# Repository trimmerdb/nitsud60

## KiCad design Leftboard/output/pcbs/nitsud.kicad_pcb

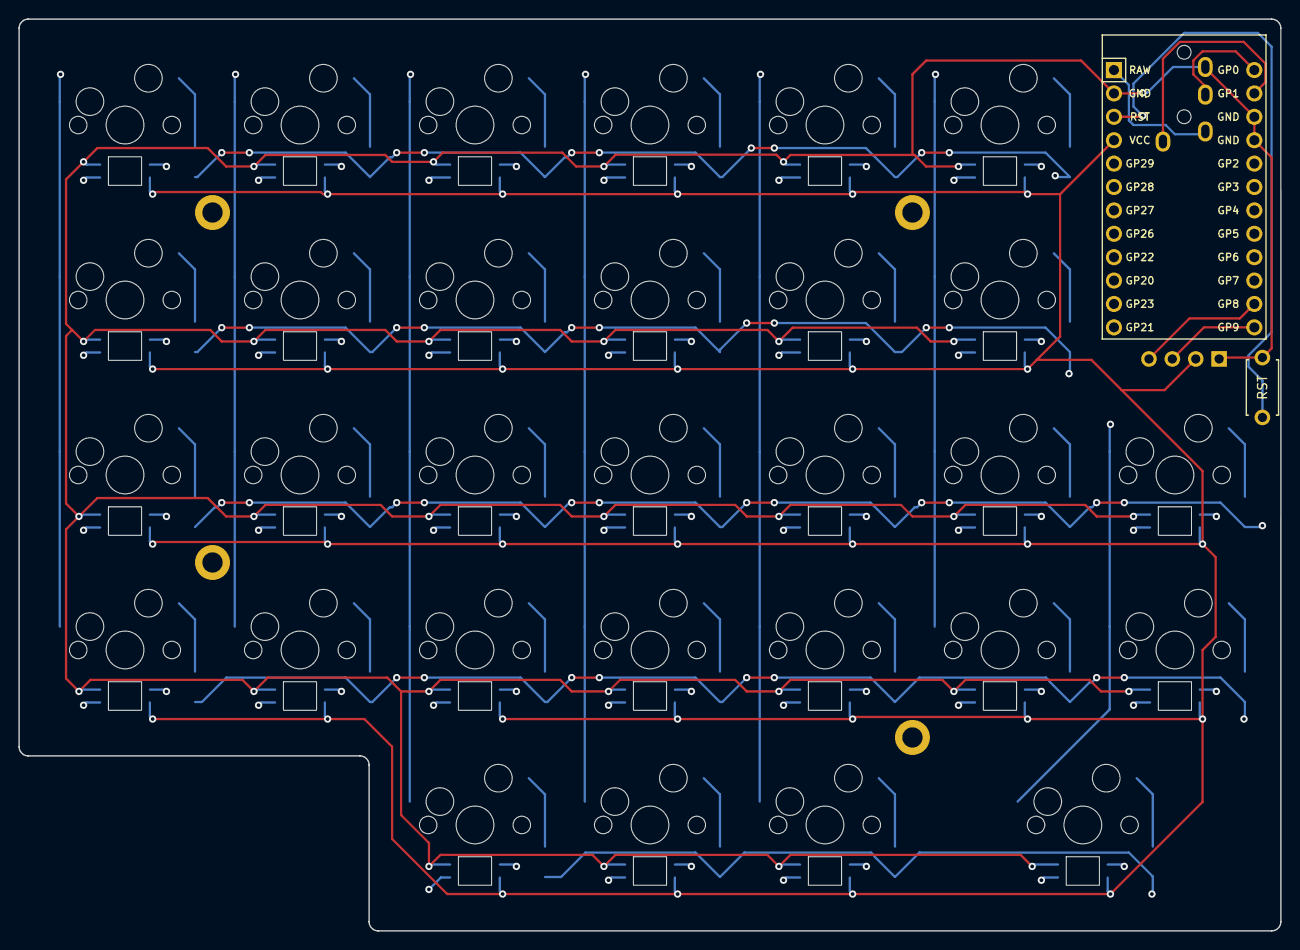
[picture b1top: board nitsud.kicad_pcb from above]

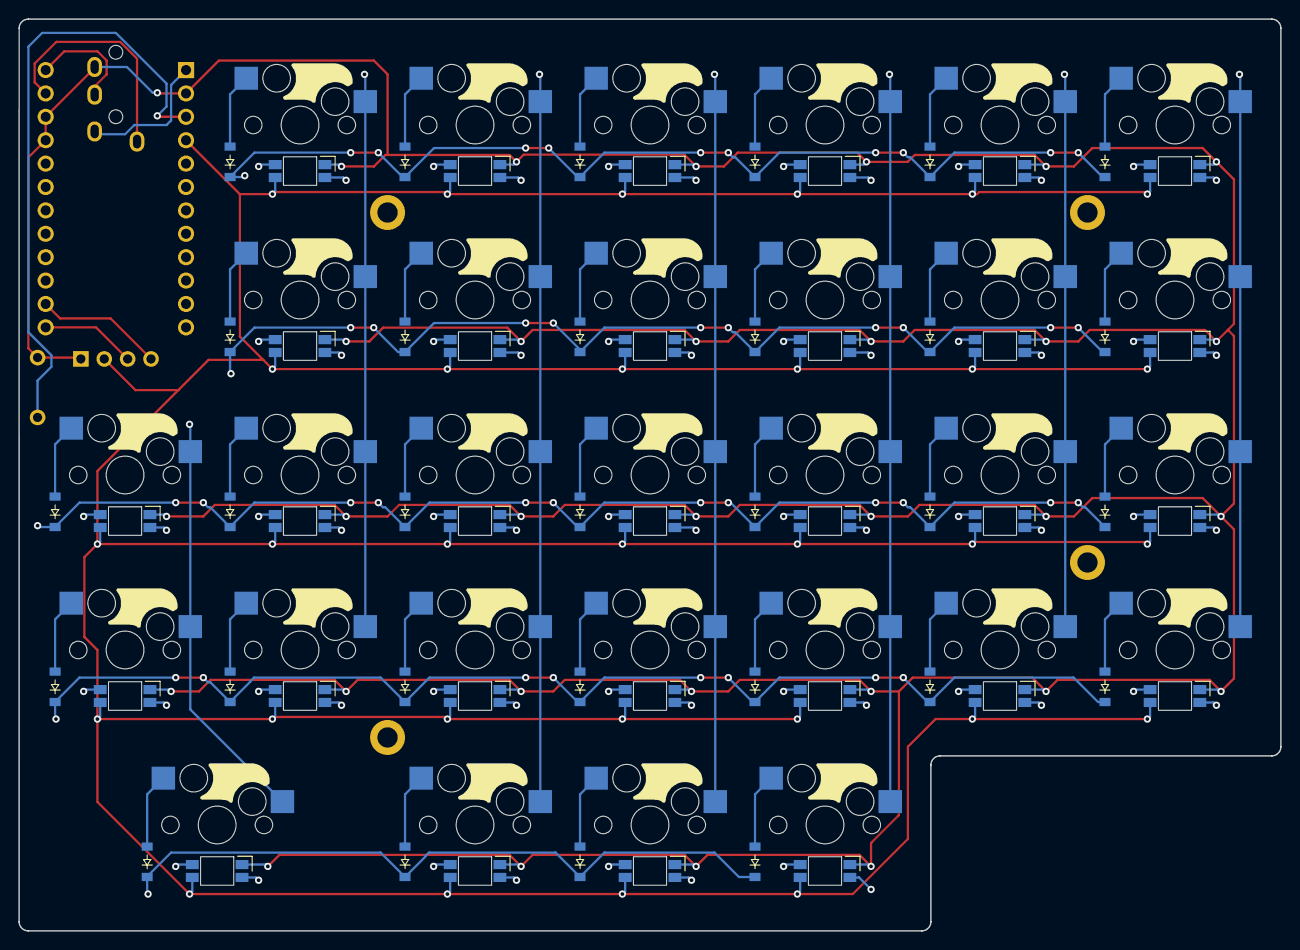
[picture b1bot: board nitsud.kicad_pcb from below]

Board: 4 copper layers, 137.0 x 99.0 mm, 98 parts (90 on the bottom side), 51 nets.

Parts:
D1, D2, D3, D4, D5, D6, D7, D8, D9, D10, D11, D12, D13, D14, D15, D16, D17, D18, D19, D20, D21, D22, D23, D24, D25, D26, D27, D28, D29, D30: diode_tht_sod123
H1, H2, H3, H4: mounting_hole_plated
LED1, LED2, LED3, LED4, LED5, LED6, LED7, LED8, LED9, LED10, LED11, LED12, LED13, LED14, LED15, LED16, LED17, LED18, LED19, LED20, LED21, LED22, LED23, LED24, LED25, LED26, LED27, LED28, LED29, LED30: led_SK6812mini-e (per-keysingle-side)
MCU1: ProMicro
OLED1: OLED; OLED_headers
RST1: reset_switch_tht_top
S1, S2, S3, S4, S5, S6, S7, S8, S9, S10, S11, S12, S13, S14, S15, S16, S17, S18, S19, S20, S21, S22, S23, S24, S25, S26, S27, S28, S29, S30: switch_mx
TRRS1: trrs_pj320a

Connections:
GND: LED1.3, LED2.3, LED3.3, LED4.3, LED5.3, LED6.3, LED7.3, LED8.3, LED9.3, LED10.3, LED11.3, LED12.3, LED13.3, LED14.3, LED15.3, LED16.3, LED17.3, LED18.3, LED19.3, LED20.3, LED21.3, LED22.3, LED23.3, LED24.3, LED25.3, LED26.3, LED27.3, LED28.3, LED29.3, LED30.3, MCU1.2, MCU1.15, MCU1.16, OLED1.1, RST1.2, TRRS1.2
P0: MCU1.14, TRRS1.5
P1: MCU1.13, TRRS1.3
P2: D24.1, MCU1.17
P3: D23.1, MCU1.18
P4: D26.1, MCU1.19
P5: D25.1, MCU1.20
P6: D30.1, MCU1.21
P8: MCU1.23, OLED1.4
P9: MCU1.24, OLED1.3
P10: LED24.4, MCU1.12
P14: MCU1.10, S24.1
P15: MCU1.9, S20.1
P16: MCU1.11, S26.1
P18: MCU1.8, S16.1
P19: MCU1.7, S12.1
P20: MCU1.6, S8.1
P21: MCU1.5, S4.1
RAW: MCU1.1, TRRS1.4
RST: MCU1.3, RST1.1
VCC: LED1.1, LED2.1, LED3.1, LED4.1, LED5.1, LED6.1, LED7.1, LED8.1, LED9.1, LED10.1, LED11.1, LED12.1, LED13.1, LED14.1, LED15.1, LED16.1, LED17.1, LED18.1, LED19.1, LED20.1, LED21.1, LED22.1, LED23.1, LED24.1, LED25.1, LED26.1, LED27.1, LED28.1, LED29.1, LED30.1, MCU1.4, OLED1.2
far_default: D29.2, S29.2
home_default: D28.2, S28.2
index_bottom: D13.2, S13.2
index_home: D14.2, S14.2
index_middle: D15.2, S15.2
index_top: D16.2, S16.2
inner_bottom: D17.2, S17.2
inner_home: D18.2, S18.2
inner_middle: D19.2, S19.2
inner_top: D20.2, S20.2
middle_bottom: D9.2, S9.2
middle_home: D10.2, S10.2
middle_middle: D11.2, S11.2
middle_top: D12.2, S12.2
morefar_default: D30.2, S30.2
mostouter_bottom: D25.2, S25.2
mostouter_home: D26.2, S26.2
near_default: D27.2, S27.2
outer_bottom: D21.2, S21.2
outer_home: D22.2, S22.2
outer_middle: D23.2, S23.2
outer_top: D24.2, S24.2
pinky_bottom: D1.2, S1.2
pinky_home: D2.2, S2.2
pinky_middle: D3.2, S3.2
pinky_top: D4.2, S4.2
ring_bottom: D5.2, S5.2
ring_home: D6.2, S6.2
ring_middle: D7.2, S7.2
ring_top: D8.2, S8.2

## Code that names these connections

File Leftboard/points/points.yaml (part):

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        autobind: 10
        skip: false
        asym: both
        colrow: pinky_bottom
        name: matrix_pinky_bottom
        zone:
            key:
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        autobind: 10
        skip: false
        asym: both
        colrow: pinky_home
        name: matrix_pinky_home
        zone:
            key:
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        autobind: 10
        skip: false
        asym: both
        colrow: pinky_top
        name: matrix_pinky_top
        zone:
            key:
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        autobind: 10
        skip: false
        asym: both
        colrow: pinky_middle
        name: matrix_pinky_middle
        zone:
            key:
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
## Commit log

2025-01-25 First Commit - Left board progress
2025-01-25 addded correct outline and pcb
2025-01-25 board generation
2025-01-25 Reconfigured the stuff and added case
2025-01-27 figured .yaml is needed
2025-01-27 stl created
2025-01-27 changing diode
2025-01-27 hot swap sockets
2025-01-28 added reset, led, trrs
2025-01-28 routing time
2025-01-28 made it a workspace
2025-01-28 routing
2025-01-29 Gerbers Created and added fix to edgecut
2025-01-30 switch plate
2025-01-30 switch plate fix
2025-02-03 trace fix
